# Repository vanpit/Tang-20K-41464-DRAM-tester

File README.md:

Tang Primer 20K & Tang Nano 20K 41464 DRAM Tester

Timing resolution is 5.29ns for Primer 20K version and 6.06ns for Nano 20K version

- 8 different patterns WRITE/READ
- MATS+
- 4ms (datasheet) data retention 

BOM:

- Tang Primer 20K + Lite dock + PMOD LEDx8 module + Sipeed RV Debugger Plus
  - OR
- Tang Nano 20K
  - AND  
- U1, U2: SN74AHCT245PWR
- U3: SN74LVC8T245PW
- U4: MIC94090YC6-TR
- LED SMD 0805 ex. IN-S85CS5R
- R1, R2: 5K Ohm Resistor SMD 0805
- R3..R10: 33 Ohm Resistor SMD 0805
- R11..R14, R16: 10K Ohm Resistor SMD 0805
- R15: 1K Ohm Resistor SMD 0805
- R17..R24: 0 Ohm OR 33 Ohm Resistor SMD 0805
- C1..C7: 100nF 0805 Capacitor
- ZIF Socket 18 pin
- 40 pin (2x20) 90 deg female connector (ZL263-40DG) (Tang Primer only)
- 2x 20 male/female pin headers (Tang Nano only)
- 18 pin (1x18) 90 deg male connector (optional, for debug)

How to use:

- Assembly guide - Pictures
- Synthetize and program Tang with Gowin IDE.
  - For Primer 20K version use "Tang 41464 tester-1.1.zip" gerber files and "Tang 41464 dram tester" firmware project
  - For Nano 20K version use  "Tang 41464 tester Nano 1.1.zip" gerber files and "Tang 41464 dram tester Nano" firmware project
  - IMPORTANT! For Nano 20K version set "pll_clk O0=33M" in BL616 config as project use 10 PIN FPGA 33MHz clock 
- Connect to uart module serial port with 115200 baud rate

Terminal keys
- "1", "2", "3", "4": select dram class speed test 80ns, 100ns, 120ns, 150ns
- "q", "Q": increase/decrease test repetition count (0x03FF reps takes about 10 minutes)
- "w": enable/disable 4ms delay/data retention test between write and read operations
- "c": show current test config
- "r" / lite dock T2 button / Nano 20K S1 button: start test

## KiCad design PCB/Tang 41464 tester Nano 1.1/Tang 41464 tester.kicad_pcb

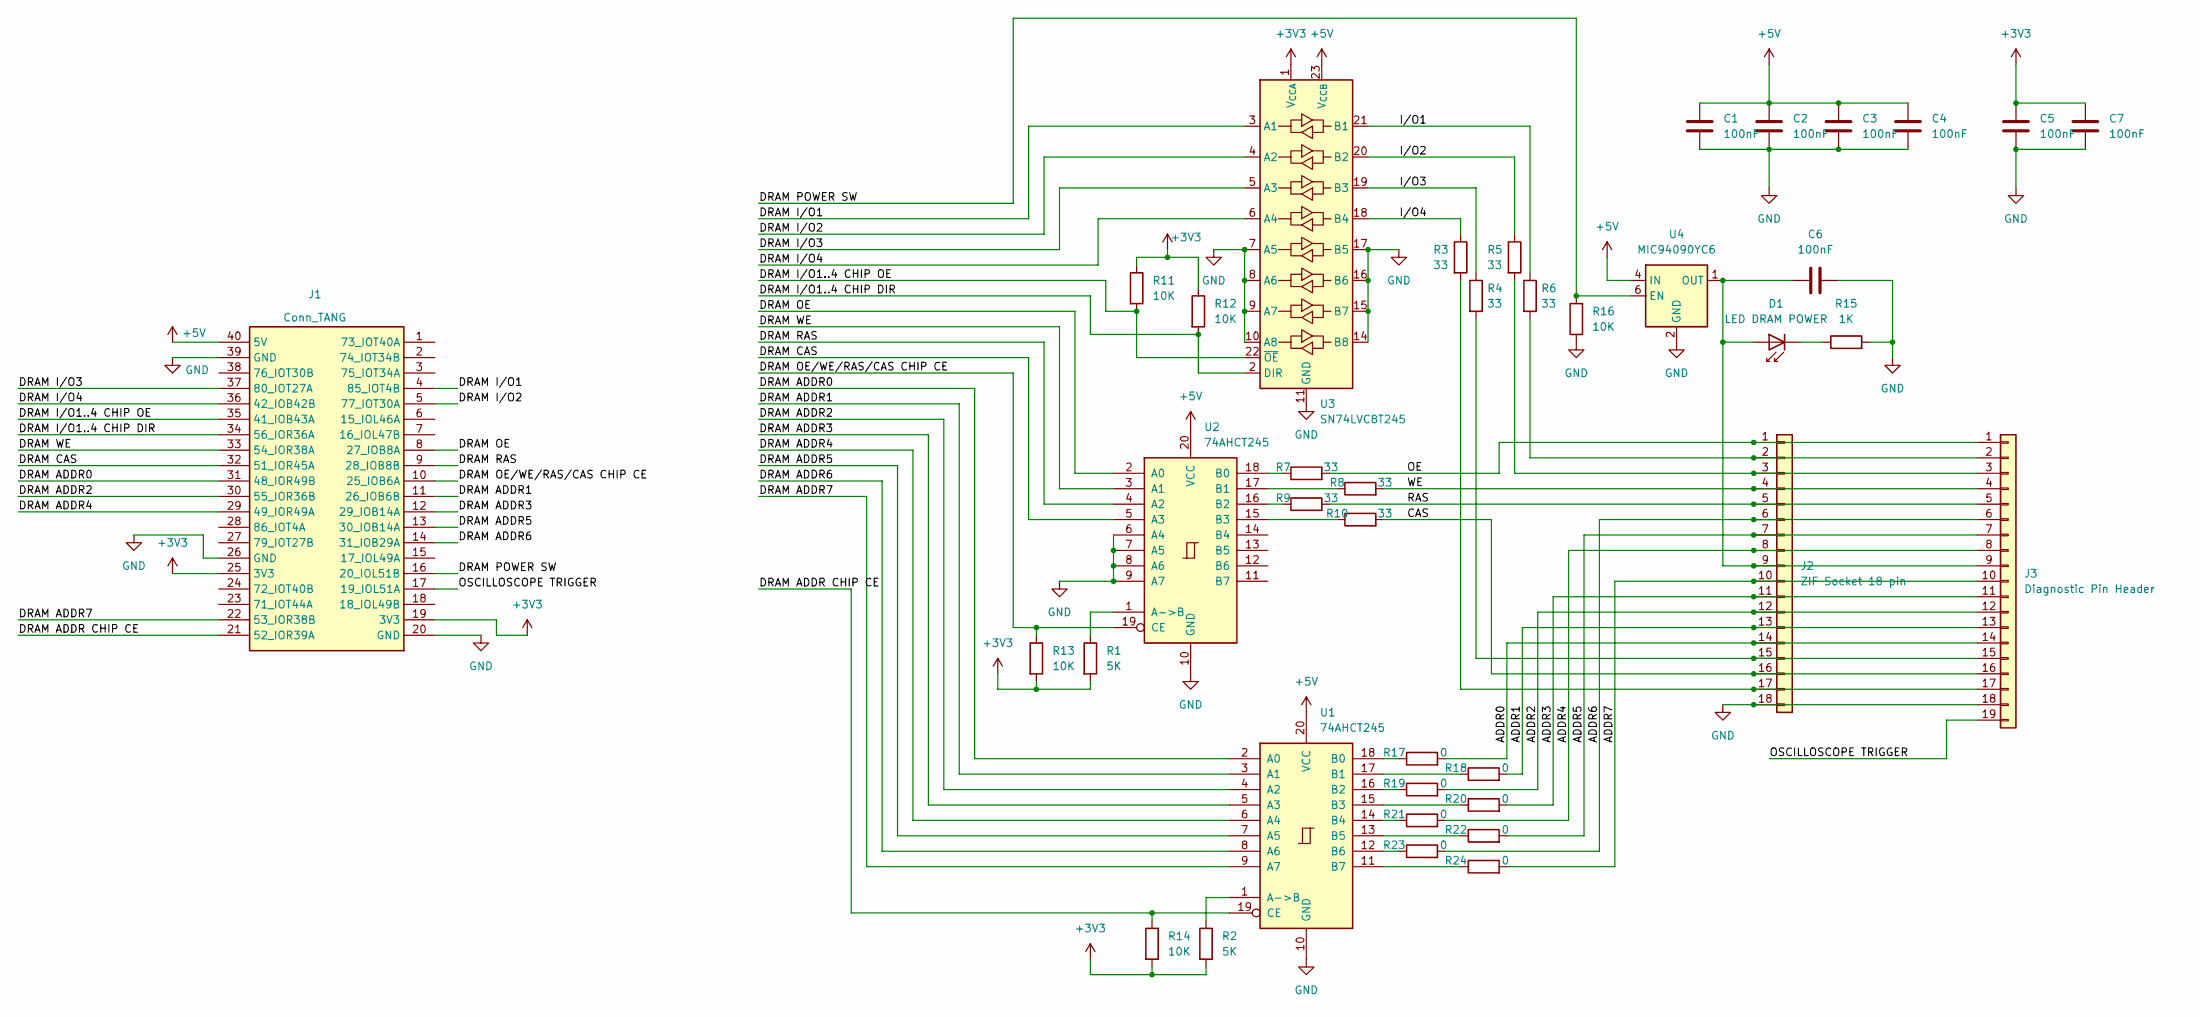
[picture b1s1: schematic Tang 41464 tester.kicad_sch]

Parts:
C1, C2, C3, C4, C5, C6, C7: 100nF; C_0805_2012Metric
D1: LED DRAM POWER; LED_0805_2012Metric
J1: Conn_TANG; DIP-40_TangNano20K
J2: ZIF Socket 18 pin; DIP-18_W7.62mm_Socket_LongPads
J3: Diagnostic Pin Header; PinHeader_1x19_P2.54mm_Horizontal
R1, R2: 5K; R_0805_2012Metric
R3, R4, R5, R6, R7, R8, R9, R10: 33; R_0805_2012Metric
R11, R12, R13, R14, R16: 10K; R_0805_2012Metric
R15: 1K; R_0805_2012Metric
R17, R18, R19, R20, R21, R22, R23, R24: 0; R_0805_2012Metric
U1, U2: 74AHCT245; TSSOP-20_4.4x6.5mm_P0.65mm
U3: SN74LVC8T245; TSSOP-24_4.4x7.8mm_P0.65mm
U4: MIC94090YC6; SOT-363_SC-70-6

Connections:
+3V3: C5.1, C7.1, J1.19 (3V3), J1.25 (3V3), R1.2, R2.2, R11.1, R12.1, R13.2, R14.2, U3.1 (V_{CCA})
+5V: C1.1, C2.1, C3.1, C4.1, J1.40 (5V), U1.20 (VCC), U2.20 (VCC), U3.23 (V_{CCB}), U3.24 (V_{CCB}), U4.4 (IN)
/ADDR0: J2.14, J3.14, R17.2
/ADDR1: J2.13, J3.13, R18.2
/ADDR2: J2.12, J3.12, R19.2
/ADDR3: J2.11, J3.11, R20.2
/ADDR4: J2.8, J3.8, R21.2
/ADDR5: J2.7, J3.7, R22.2
/ADDR6: J2.6, J3.6, R23.2
/ADDR7: J2.10, J3.10, R24.2
/CAS: J2.16, J3.16, R10.2
/DRAM ADDR0: J1.31 (48_IOR49B), U1.2 (A0)
/DRAM ADDR1: J1.11 (26_IOB6B), U1.3 (A1)
/DRAM ADDR2: J1.30 (55_IOR36B), U1.4 (A2)
/DRAM ADDR3: J1.12 (29_IOB14A), U1.5 (A3)
/DRAM ADDR4: J1.29 (49_IOR49A), U1.6 (A4)
/DRAM ADDR5: J1.13 (30_IOB14A), U1.7 (A5)
/DRAM ADDR6: J1.14 (31_IOB29A), U1.8 (A6)
/DRAM ADDR7: J1.22 (53_IOR38B), U1.9 (A7)
/DRAM ADDR CHIP CE: J1.21 (52_IOR39A), R14.1, U1.19 (CE)
/DRAM CAS: J1.32 (51_IOR45A), U2.5 (A3)
/DRAM I/O1: J1.4 (85_IOT4B), U3.3 (A1)
/DRAM I/O1..4 CHIP DIR: J1.34 (56_IOR36A), R12.2, U3.2 (DIR)
/DRAM I/O1..4 CHIP OE: J1.35 (41_IOB43A), R11.2, U3.22 (~OE)
/DRAM I/O2: J1.5 (77_IOT30A), U3.4 (A2)
/DRAM I/O3: J1.37 (80_IOT27A), U3.5 (A3)
/DRAM I/O4: J1.36 (42_IOB42B), U3.6 (A4)
/DRAM OE: J1.8 (27_IOB8A), U2.2 (A0)
/DRAM OE/WE/RAS/CAS CHIP CE: J1.10 (25_IOB6A), R13.1, U2.19 (CE)
/DRAM POWER SW: J1.16 (20_IOL51B), R16.2, U4.6 (EN)
/DRAM RAS: J1.9 (28_IOB8B), U2.4 (A2)
/DRAM WE: J1.33 (54_IOR38A), U2.3 (A1)
/I/O1: R6.1, U3.21 (B1)
/I/O2: R5.1, U3.20 (B2)
/I/O3: R4.1, U3.19 (B3)
/I/O4: R3.1, U3.18 (B4)
/OE: J2.1, J3.1, R7.2
/OSCILLOSCOPE TRIGGER: J1.17 (19_IOL51A), J3.19
/RAS: J2.5, J3.5, R9.2
/WE: J2.4, J3.4, R8.2
GND: C1.2, C2.2, C3.2, C4.2, C5.2, C6.2, C7.2, J1.20 (GND), J1.26 (GND), J1.39 (GND), J2.18, J3.18, R15.2, R16.1, U1.10 (GND), U2.6 (A4), U2.7 (A5), U2.8 (A6), U2.9 (A7), U2.10 (GND), U3.7 (A5), U3.8 (A6), U3.9 (A7), U3.10 (A8), U3.11 (GND), U3.12 (GND), U3.13 (GND), U3.14 (B8), U3.15 (B7), U3.16 (B6), U3.17 (B5), U4.2 (GND), U4.5 (GND)
unnamed: C6.1, D1.2 (A), J2.9, J3.9, U4.1 (OUT)
unnamed: D1.1 (K), R15.1
unnamed: J2.2, J3.2, R6.2
unnamed: J2.3, J3.3, R5.2
unnamed: J2.15, J3.15, R4.2
unnamed: J2.17, J3.17, R3.2
unnamed: R2.1, U1.1 (A->B)
unnamed: R17.1, U1.18 (B0)
unnamed: R18.1, U1.17 (B1)
unnamed: R19.1, U1.16 (B2)
unnamed: R20.1, U1.15 (B3)
unnamed: R21.1, U1.14 (B4)
unnamed: R22.1, U1.13 (B5)
unnamed: R23.1, U1.12 (B6)
unnamed: R24.1, U1.11 (B7)
unnamed: R1.1, U2.1 (A->B)
unnamed: R7.1, U2.18 (B0)
unnamed: R8.1, U2.17 (B1)
unnamed: R9.1, U2.16 (B2)
unnamed: R10.1, U2.15 (B3)

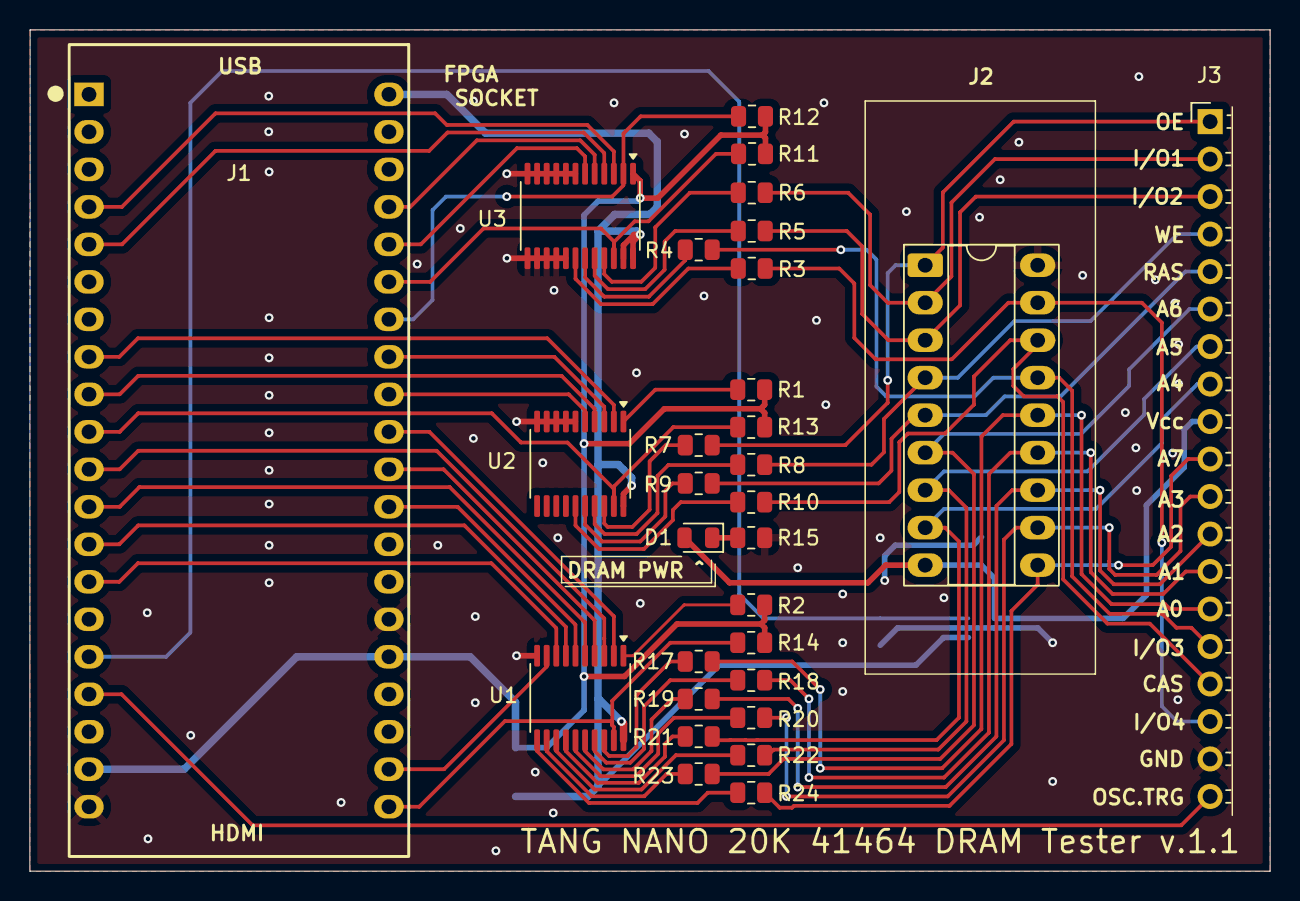
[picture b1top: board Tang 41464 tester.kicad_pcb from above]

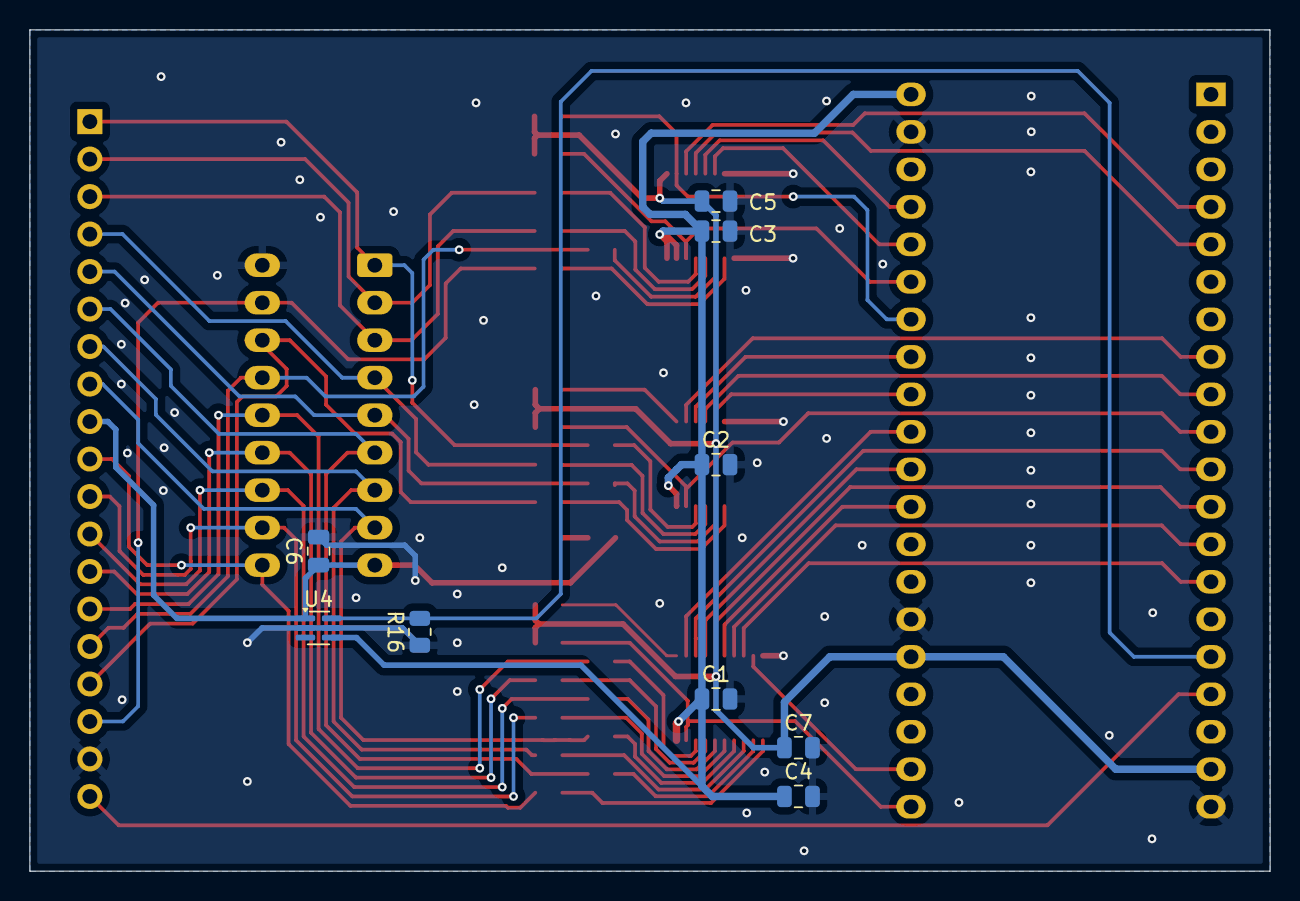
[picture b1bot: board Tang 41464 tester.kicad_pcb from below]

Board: 2 copper layers, 84.0 x 57.0 mm, 39 parts (9 on the bottom side), 61 nets.

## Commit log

2026-03-16 Add README for Tang Primer DRAM Tester
    Added detailed information about the Tang Primer DRAM Tester, including BOM, usage instructions, and terminal keys.
2026-03-16 Update BOM with new module details
2026-03-16 Update README with ZIF socket and connector details
    Added information about ZIF socket and connectors.
2026-03-17 Update README for clarity on test repetitions
2026-03-17 Gerber files added
2026-03-17 Fix language detection
2026-03-17 Fix typo in resistor value from 'O' to '0'
2026-03-17 Cleanup repo
2026-03-17 Language detection fix
2026-03-24 Added tester Nano version for Tang 20K Nano FPGA
2026-03-24 Added tester Nano Picture
2026-03-24 Correct gerber upload for Nano version
2026-03-24 Revise README for Tang Primer and Nano 20K details
    Updated README with details for Tang Primer 20K and Nano 20K DRAM Tester, including timing resolution, BOM changes, and usage instructions.
2026-03-24 Fix formatting of BOM section in README
2026-03-24 Fix formatting in README.md for component list
2026-03-24 Clarify component list formatting in README
2026-03-24 Update README with clarification on FPGA clock settings
